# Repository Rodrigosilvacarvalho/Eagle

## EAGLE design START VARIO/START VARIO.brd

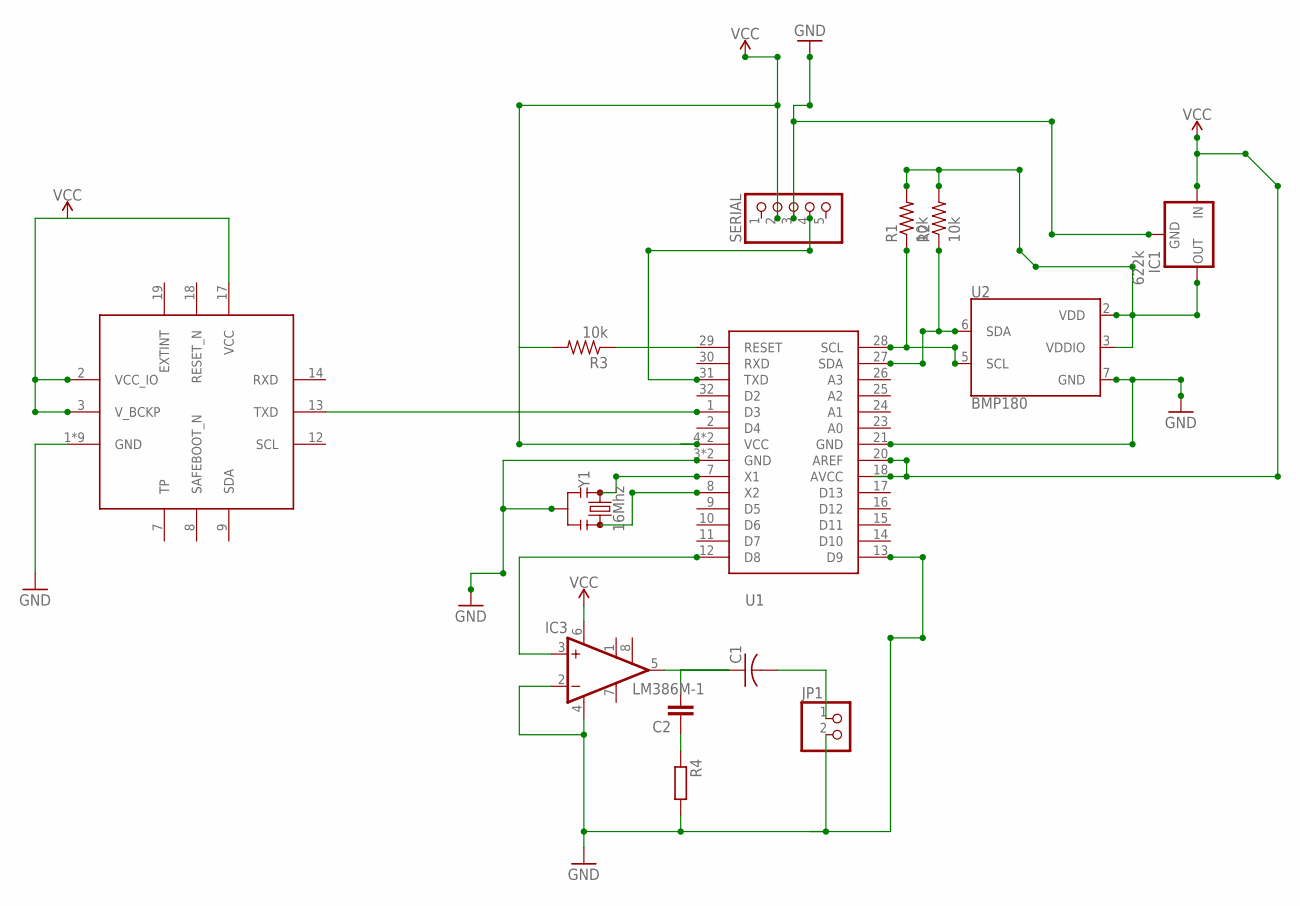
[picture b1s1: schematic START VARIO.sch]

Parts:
C1: C-USC1608; C1608
C2: C-EUC0805; C0805
IC1: 622k; SOT23
IC2: SAM-M8Q
IC3: LM386M-1; SO08
JP1: PINHD-1X2; 1X02
R1: 10k; R0805
R2, R3: 10k; 0603-RES
R4: R-EU_R0805; R0805
SERIAL: PINHD-1X5; 1X05
U1: ATMEGA328P; TQFP32-08
U2: BMP180
Y1: 16Mhz; RESONATOR-SMD-3.2X1.3

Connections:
CN1: SERIAL.4, U1.31 (TXD)
GND: IC1.1 (GND), IC2.1 (GND), IC2.4 (GND), IC2.5 (GND), IC2.6 (GND), IC2.10 (GND), IC2.11 (GND), IC2.15 (GND), IC2.16 (GND), IC2.20 (GND), IC3.2 (-IN), IC3.4 (GND), JP1.2, R4.2, SERIAL.3, U1.3 (GND), U1.5 (GND), U1.13 (D9), U1.21 (GND), U2.7 (GND), Y1.2
unnamed: R2.1, U1.27 (SDA), U2.6 (SDA)
unnamed: R1.1, U1.28 (SCL), U2.5 (SCL)
unnamed: C1.1, C2.2, IC3.5 (OUT)
unnamed: IC3.3 (+IN), U1.12 (D8)
unnamed: C1.2, JP1.1
unnamed: U1.7 (X1), Y1.1
unnamed: U1.8 (X2), Y1.3
unnamed: IC1.2 (OUT), R1.2, R2.2, U2.2 (VDD), U2.3 (VDDIO)
unnamed: C2.1, R4.1
unnamed: R3.1, U1.29 (RESET)
unnamed: IC2.13 (TXD), U1.1 (D3)
VCC: IC1.3 (IN), IC2.2 (VCC_IO), IC2.3 (V_BCKP), IC2.17 (VCC), IC3.6 (VS), R3.2, SERIAL.2, U1.4 (VCC), U1.6 (VCC), U1.18 (AVCC), U1.20 (AREF)

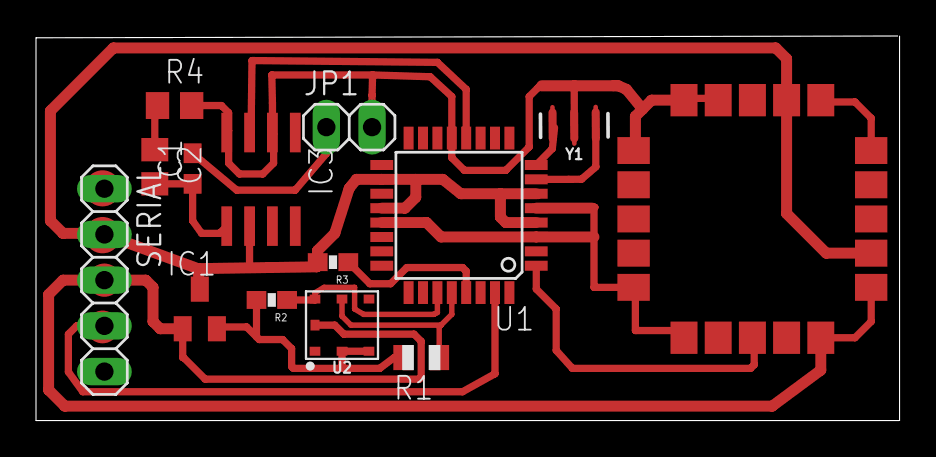
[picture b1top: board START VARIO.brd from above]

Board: 2 copper layers, 48.0 x 21.4 mm, 14 parts (0 on the bottom side), 14 nets.

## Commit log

2021-09-24 Up
    Subindo Arquivos para Github
2021-09-24 Up
    Arquivos de Config Cad Eagle
2021-09-25 UP
    Atualizando Repositorios

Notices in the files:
parts and their libraries:
SparkFun-Clocks: Licensing: Creative Commons ShareAlike 4.0 International - https://creativecommons.org/licenses/by-sa/4.0
SparkFun-Passives: Licensing: CC v3.0 Share-Alike You are welcome to use this library for commercial purposes.
